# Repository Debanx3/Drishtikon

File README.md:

# Drishtikon:
## EdgeAI based human detection system <br>
 
+ The beginnings: ***Drishtikon*** is a framework consisting of two modules, the mainboard and the controller modules that can be powered directly from the 220VAC mains in dorms, libraries and canteens. The two boards communicate with each other using a BLE protocol and the mainboard is connected to the internet via Wi-Fi, it connects to the local network using hard coding.<br> <br>
  <div>

  </div>

* License: MIT License
* Contact/Credits: Debanil Chanda, [DebanX3@github.com](mailto:debanx3@github.com)

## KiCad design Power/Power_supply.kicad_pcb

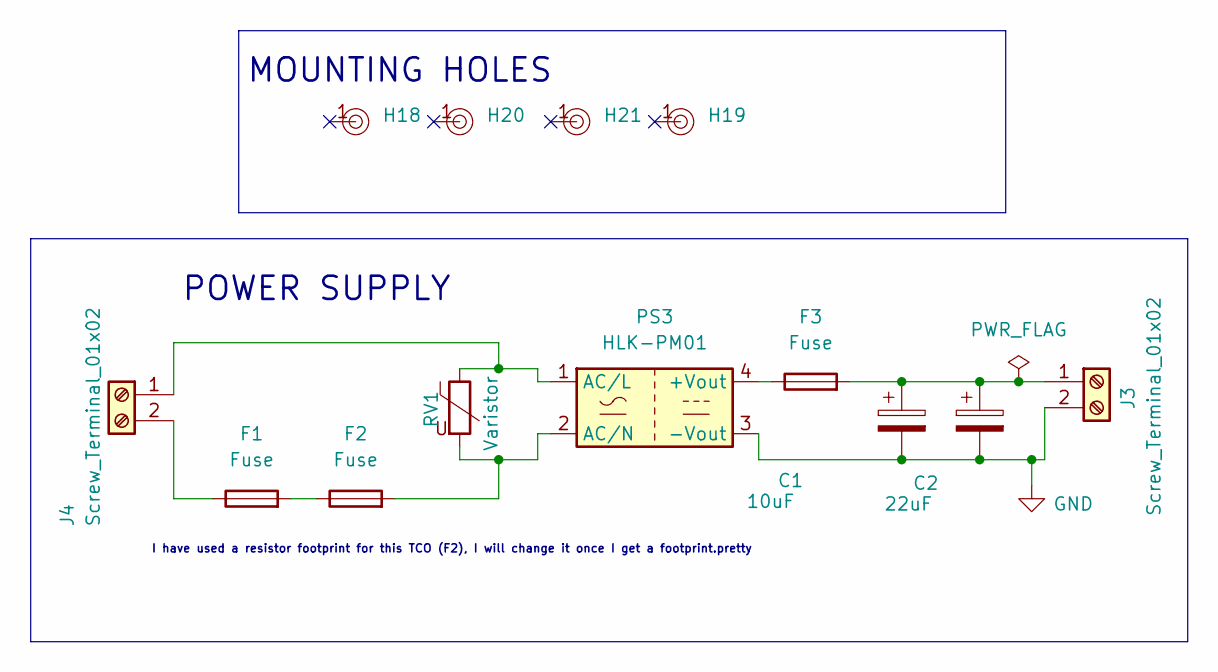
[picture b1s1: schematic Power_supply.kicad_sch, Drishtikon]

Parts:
C1: 10uF; CP_Radial_D8.0mm_P3.50mm
C2: 22uF; CP_Radial_D8.0mm_P3.50mm
F1, F3: Fuse; Fuseholder_Cylinder-5x20mm_Stelvio-Kontek_PTF78_Horizontal_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
F2: Fuse; R_Axial_DIN0309_L9.0mm_D3.2mm_P12.70mm_Horizontal
H18, H19, H20, H21: Hole, 3mm
J3, J4: Screw_Terminal_01x02; TerminalBlock_Phoenix_MKDS-1,5-2-5.08_1x02_P5.08mm_Horizont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
PS3: HLK-PM01; Converter_ACDC_Hi-Link_HLK-PMxx
RV1: Varistor; RV_Disc_D12mm_W3.9mm_P7.5mm

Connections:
GND: C1.2, C2.2, J3.2, PS3.3 (-Vout)
unnamed: F1.2, F2.1
unnamed: C1.1, C2.1, F3.2, J3.1
unnamed: J4.1, PS3.1 (AC/L), RV1.1
unnamed: F1.1, J4.2
unnamed: F3.1, PS3.4 (+Vout)
unnamed: F2.2, PS3.2 (AC/N), RV1.2

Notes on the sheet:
I have used a resistor footprint for this TCO (F2), I will change it once I get a footprint.pretty
POWER SUPPLY
MOUNTING HOLES

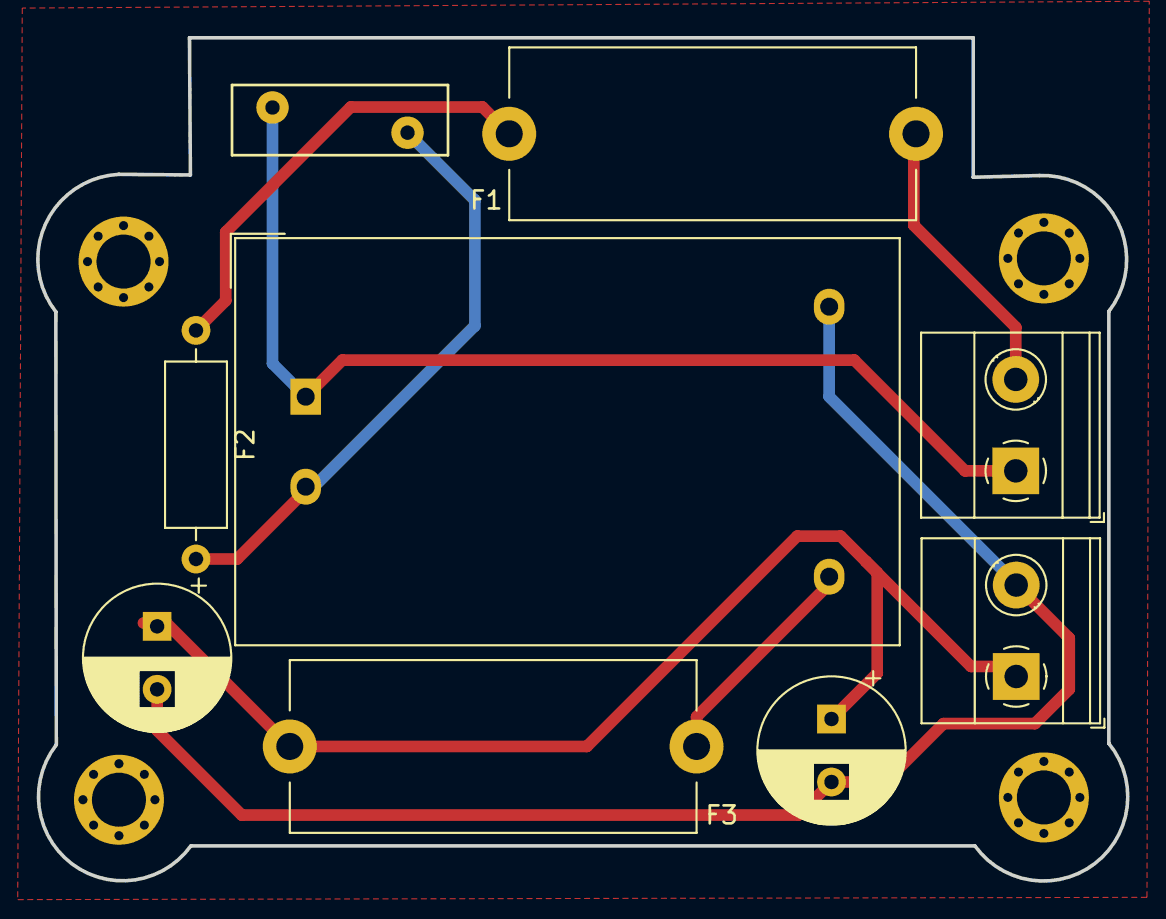
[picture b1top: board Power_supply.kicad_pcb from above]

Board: 2 copper layers, 60.6 x 46.8 mm, 13 parts (0 on the bottom side), 7 nets.

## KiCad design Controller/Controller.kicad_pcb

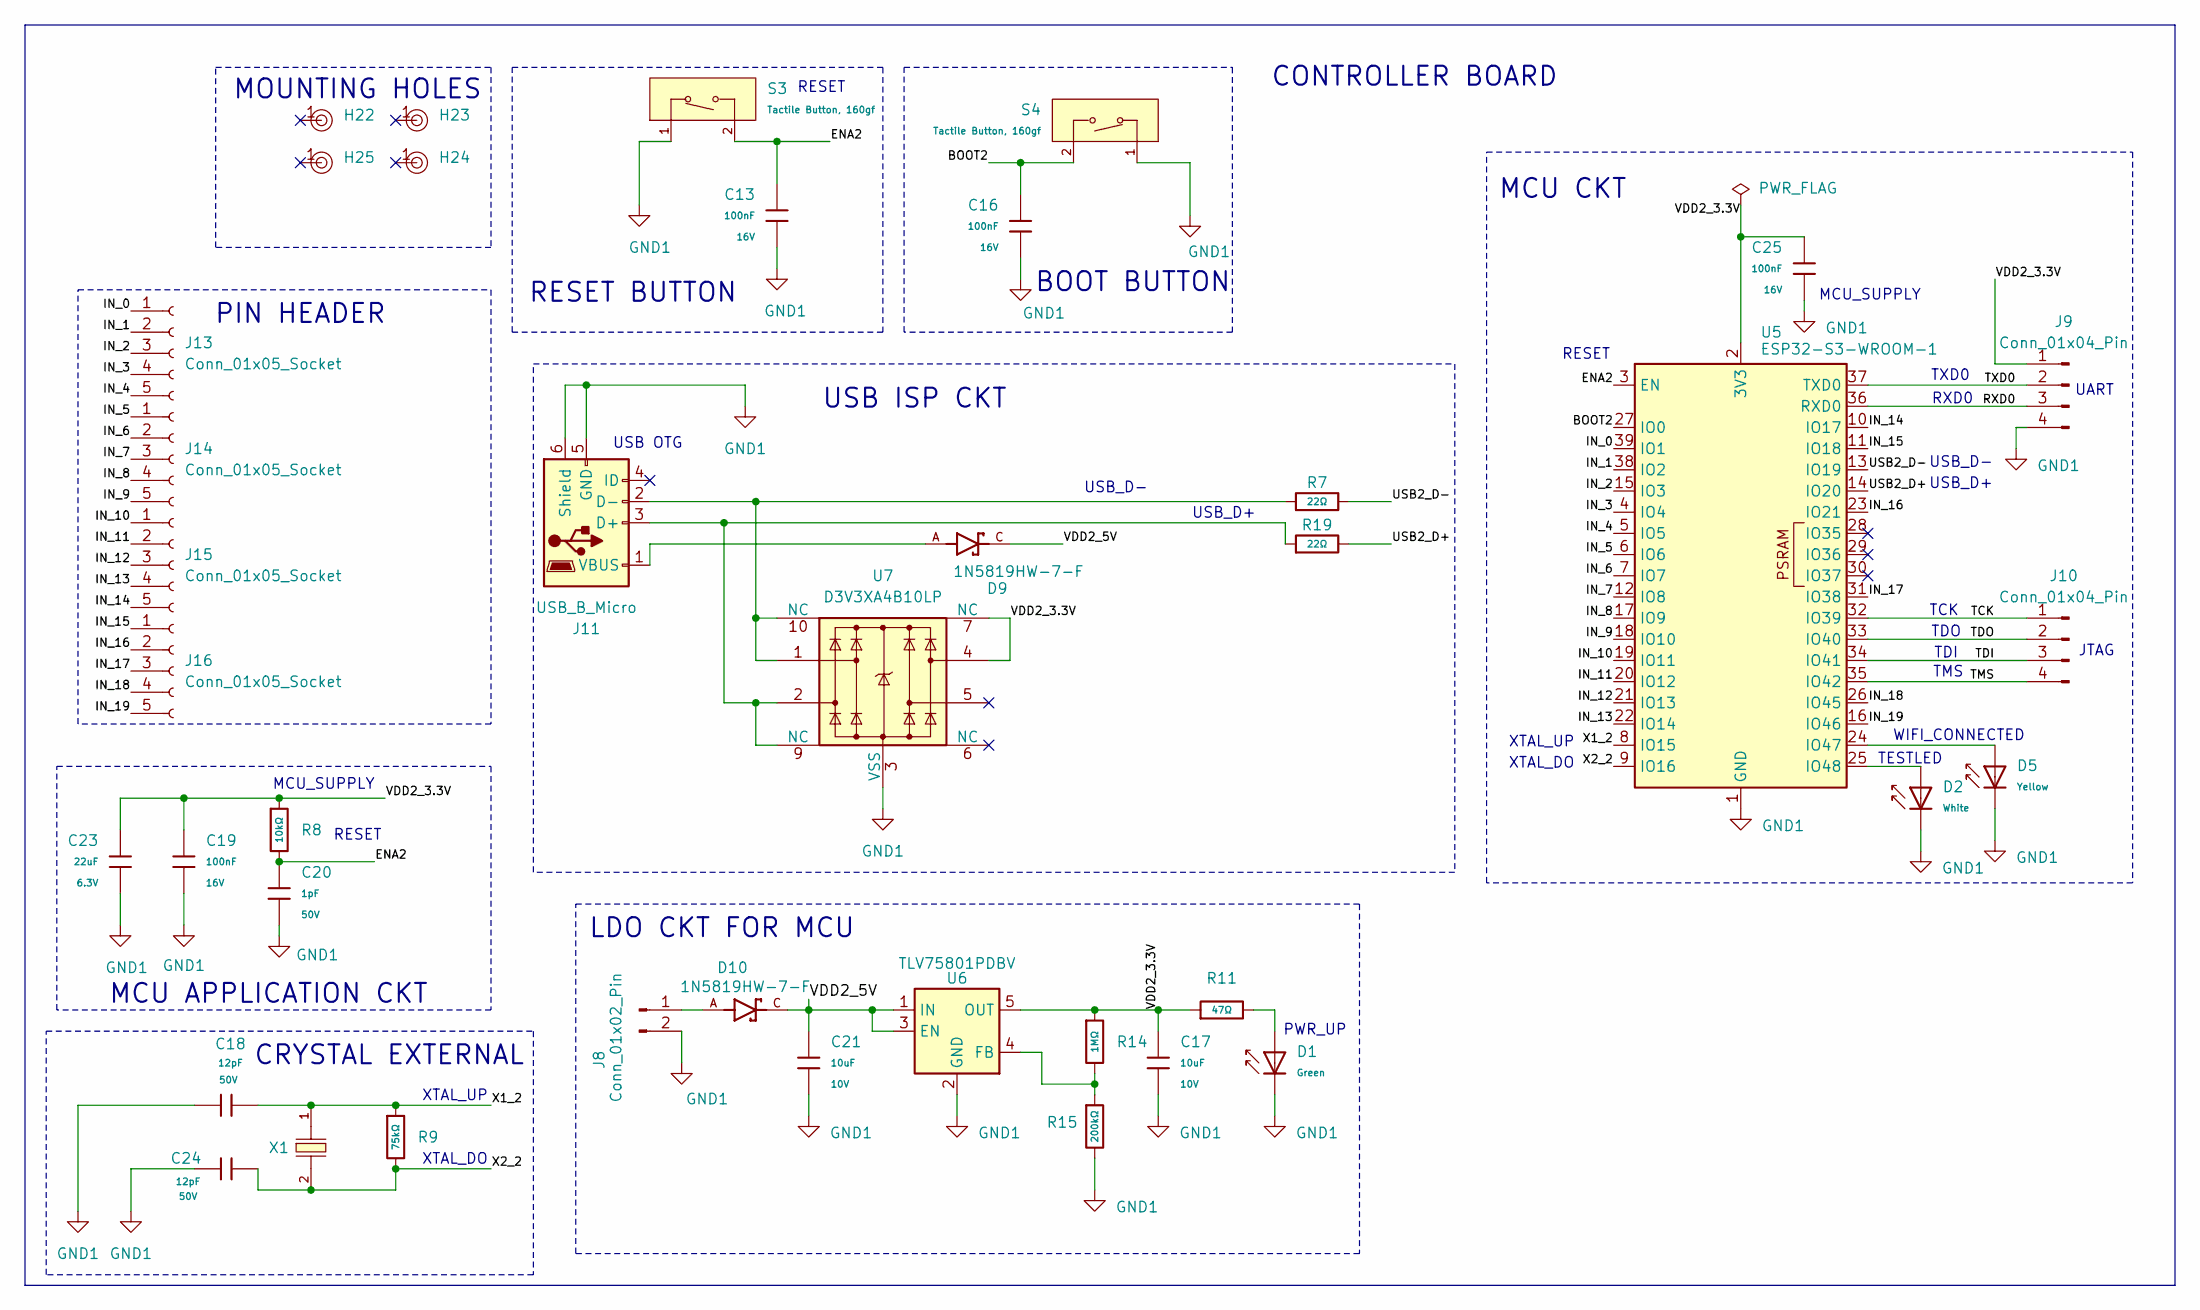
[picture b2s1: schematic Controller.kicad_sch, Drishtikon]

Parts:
C13, C16, C19, C25: 100nF; C_0402; Voltage Rated 16V; Tolerance ±10%; Part CL05B104KO5NNNC; LCSC C1525
C17, C21: 10uF; C_0603; Voltage Rated 10V; Tolerance ±10%; Part CL10A106KP8NNNC; LCSC C19702
C18, C24: 12pF; C_0402; Voltage Rated 50V; Tolerance ±5%; Part 0402CG120J500NT; LCSC C1547
C20: 1pF; C_0402; Voltage Rated 50V; Part 0402CG1R0C500NT; LCSC C1550
C23: 22uF; C_0603; Voltage Rated 6.3V; Tolerance ±20%; Part CL10A226MQ8NRNC; LCSC C59461
D1: Green; D_0805; Part KT-0805G; LCSC C2297
D2: White; D_0805; Part KT-0805W; LCSC C34499
D5: Yellow; D_0805; Part KT-0805Y; LCSC C2296
D9, D10: 1N5819HW-7-F; SOD3715X145N; PARTREV 18-2
H22, H23, H24, H25: Hole, 3mm
J8: Conn_01x02_Pin; PinHeader_1x02_P2.54mm_Horizontal
J9, J10: Conn_01x04_Pin; PinHeader_1x04_P2.54mm_Horizontal
J11: USB_B_Micro; USB_Micro-B_Molex_47346-0001
J13, J14, J15, J16: Conn_01x05_Socket; PinHeader_1x05_P2.54mm_Vertical
R7, R19: 22Ω; R_0402; Overload Voltage (Max) 50V; Tolerance ±1%; Part 0402WGF220JTCE; LCSC C25092
R8: 10kΩ; R_0402; Overload Voltage (Max) 50V; Tolerance ±1%; Part 0402WGF1002TCE; LCSC C25744
R9: 75kΩ; R_0402; Overload Voltage (Max) 50V; Tolerance ±1%; Part 0402WGF7502TCE; LCSC C25798
R11: 47Ω; R_0603; Overload Voltage (Max) 75V; Tolerance ±1%; Part 0603WAF470JT5E; LCSC C23182
R14: 1MΩ; R_0402; Overload Voltage (Max) 50V; Tolerance ±1%; Part 0402WGF1004TCE; LCSC C26083
R15: 200kΩ; R_0402; Overload Voltage (Max) 50V; Tolerance ±1%; Part 0402WGF2003TCE; LCSC C25764
S3, S4: Tactile Button, 160gf; SW_TS-1088-AR02016; Voltage Rating (Dc) 12V; Part TS-1088-AR02016; LCSC C720477
U5: ESP32-S3-WROOM-1
U6: TLV75801PDBV; SOT-23-5
U7: D3V3XA4B10LP; Diodes_UDFN-10_1.0x2.5mm_P0.5mm
X1: Q13FC1350000400; FC-135R_L3.2-W1.5; Frequency Tolerance ±20ppm; Part Q13FC13500004; LCSC C32346

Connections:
/BOOT2: C16.1, S4.2 (B), U5.27 (IO0)
/ENA2: C13.1, C20.2, R8.2, S3.2 (B), U5.3 (EN)
/IN_0: J13.1, U5.39 (IO1)
/IN_1: J13.2, U5.38 (IO2)
/IN_2: J13.3, U5.15 (IO3)
/IN_3: J13.4, U5.4 (IO4)
/IN_4: J13.5, U5.5 (IO5)
/IN_5: J14.1, U5.6 (IO6)
/IN_6: J14.2, U5.7 (IO7)
/IN_7: J14.3, U5.12 (IO8)
/IN_8: J14.4, U5.17 (IO9)
/IN_9: J14.5, U5.18 (IO10)
/IN_10: J15.1, U5.19 (IO11)
/IN_11: J15.2, U5.20 (IO12)
/IN_12: J15.3, U5.21 (IO13)
/IN_13: J15.4, U5.22 (IO14)
/IN_14: J15.5, U5.10 (IO17)
/IN_15: J16.1, U5.11 (IO18)
/IN_16: J16.2, U5.23 (IO21)
/IN_17: J16.3, U5.31 (IO38)
/IN_18: J16.4, U5.26 (IO45)
/IN_19: J16.5, U5.16 (IO46)
/RXD0: J9.3, U5.36 (RXD0)
/TCK: J10.1, U5.32 (IO39)
/TDI: J10.3, U5.34 (IO41)
/TDO: J10.2, U5.33 (IO40)
/TMS: J10.4, U5.35 (IO42)
/TXD0: J9.2, U5.37 (TXD0)
/USB2_D+: R19.2, U5.14 (IO20)
/USB2_D-: R7.2, U5.13 (IO19)
/VDD2_3.3V: C17.1, C19.1, C23.1, C25.1, J9.1, R8.1, R11.1, R14.1, U5.2 (3V3), U6.5 (OUT), U7.4, U7.7 (NC)
/VDD2_5V: C21.1, D9.C, D10.C, U6.1 (IN), U6.3 (EN)
/X1_2: C18.2, R9.1, U5.8 (IO15), X1.1
/X2_2: C24.2, R9.2, U5.9 (IO16), X1.2
GND1: C13.2, C16.2, C17.2, C18.1, C19.2, C20.1, C21.2, C23.2, C24.1, C25.2, D1.1, D2.1, D5.1, J8.2, J9.4, J11.5 (GND), J11.6 (Shield), R15.2, S3.1 (A), S4.1 (A), U5.1 (GND), U5.40 (GND), U5.41 (GND), U6.2 (GND), U7.3 (VSS), U7.8 (VSS)
unnamed: D1.2, R11.2
unnamed: D10.A, J8.1
unnamed: J11.3 (D+), R19.1, U7.2, U7.9 (NC)
unnamed: J11.2 (D-), R7.1, U7.1, U7.10 (NC)
unnamed: D9.A, J11.1 (VBUS)
unnamed: D5.2, U5.24 (IO47)
unnamed: D2.2, U5.25 (IO48)
unnamed: R14.2, R15.1, U6.4 (FB)

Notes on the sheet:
RESET
MCU_SUPPLY
UART
MCU CKT
TMS
TDI
MCU APPLICATION CKT
TDO
USB_D+
TESTLED
JTAG
BOOT BUTTON
LDO CKT FOR MCU
CONTROLLER BOARD
RESET BUTTON
WIFI_CONNECTED
MOUNTING HOLES
USB_D-
CRYSTAL EXTERNAL
XTAL_UP
PWR_UP
PIN HEADER
USB ISP CKT
USB OTG
TCK
XTAL_DO
TXD0
RXD0

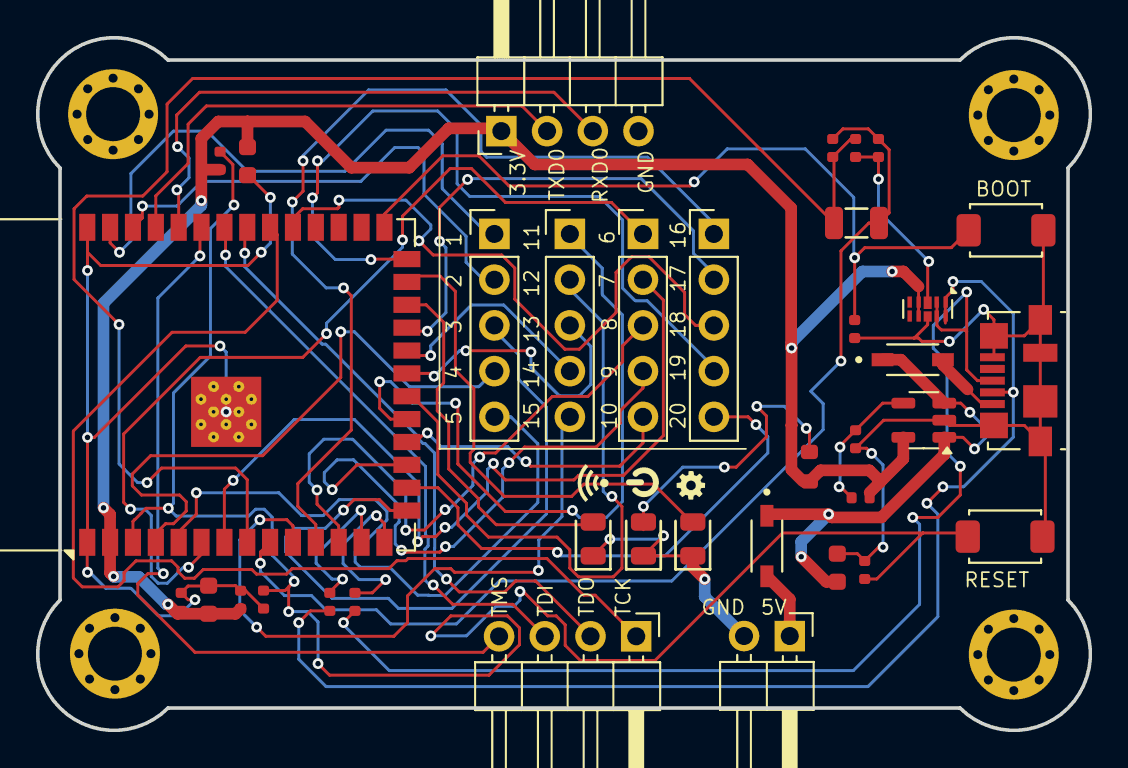
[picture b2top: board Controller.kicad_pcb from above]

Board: 4 copper layers, 58.5 x 38.5 mm, 40 parts (0 on the bottom side), 43 nets.

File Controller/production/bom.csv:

Designator,Footprint,Quantity,Value,LCSC Part #
"C13, C16, C19, C25",C_0402,4,100nF,C1525
"C17, C21",C_0603,2,10uF,C19702
"C18, C24",C_0402,2,12pF,C1547
C20,C_0402,1,1pF,C1550
C23,C_0603,1,22uF,C59461
D1,D_0805,1,Green,C2297
"D10, D9",SOD3715X145N,2,1N5819HW-7-F,
D2,D_0805,1,White,C34499
D5,D_0805,1,Yellow,C2296
"H22, H23, H24, H25","Hole, 3mm",4,~,
"J10, J9",PinHeader_1x04_P2.54mm_Horizontal,2,Conn_01x04_Pin,
J11,USB_Micro-B_Molex_47346-0001,1,USB_B_Micro,
"J13, J14, J15, J16",PinHeader_1x05_P2.54mm_Vertical,4,Conn_01x05_Socket,
J8,PinHeader_1x02_P2.54mm_Horizontal,1,Conn_01x02_Pin,
R11,R_0603,1,47Ω,C23182
R14,R_0402,1,1MΩ,C26083
R15,R_0402,1,200kΩ,C25764
"R19, R7",R_0402,2,22Ω,C25092
R8,R_0402,1,10kΩ,C25744
R9,R_0402,1,75kΩ,C25798
"S3, S4",SW_TS-1088-AR02016,2,"Tactile Button, 160gf",C720477
U5,ESP32-S3-WROOM-1,1,ESP32-S3-WROOM-1,
U6,SOT-23-5,1,TLV75801PDBV,
U7,Diodes_UDFN-10_1.0x2.5mm_P0.5mm,1,D3V3XA4B10LP,
X1,FC-135R_L3.2-W1.5,1,Q13FC1350000400,C32346

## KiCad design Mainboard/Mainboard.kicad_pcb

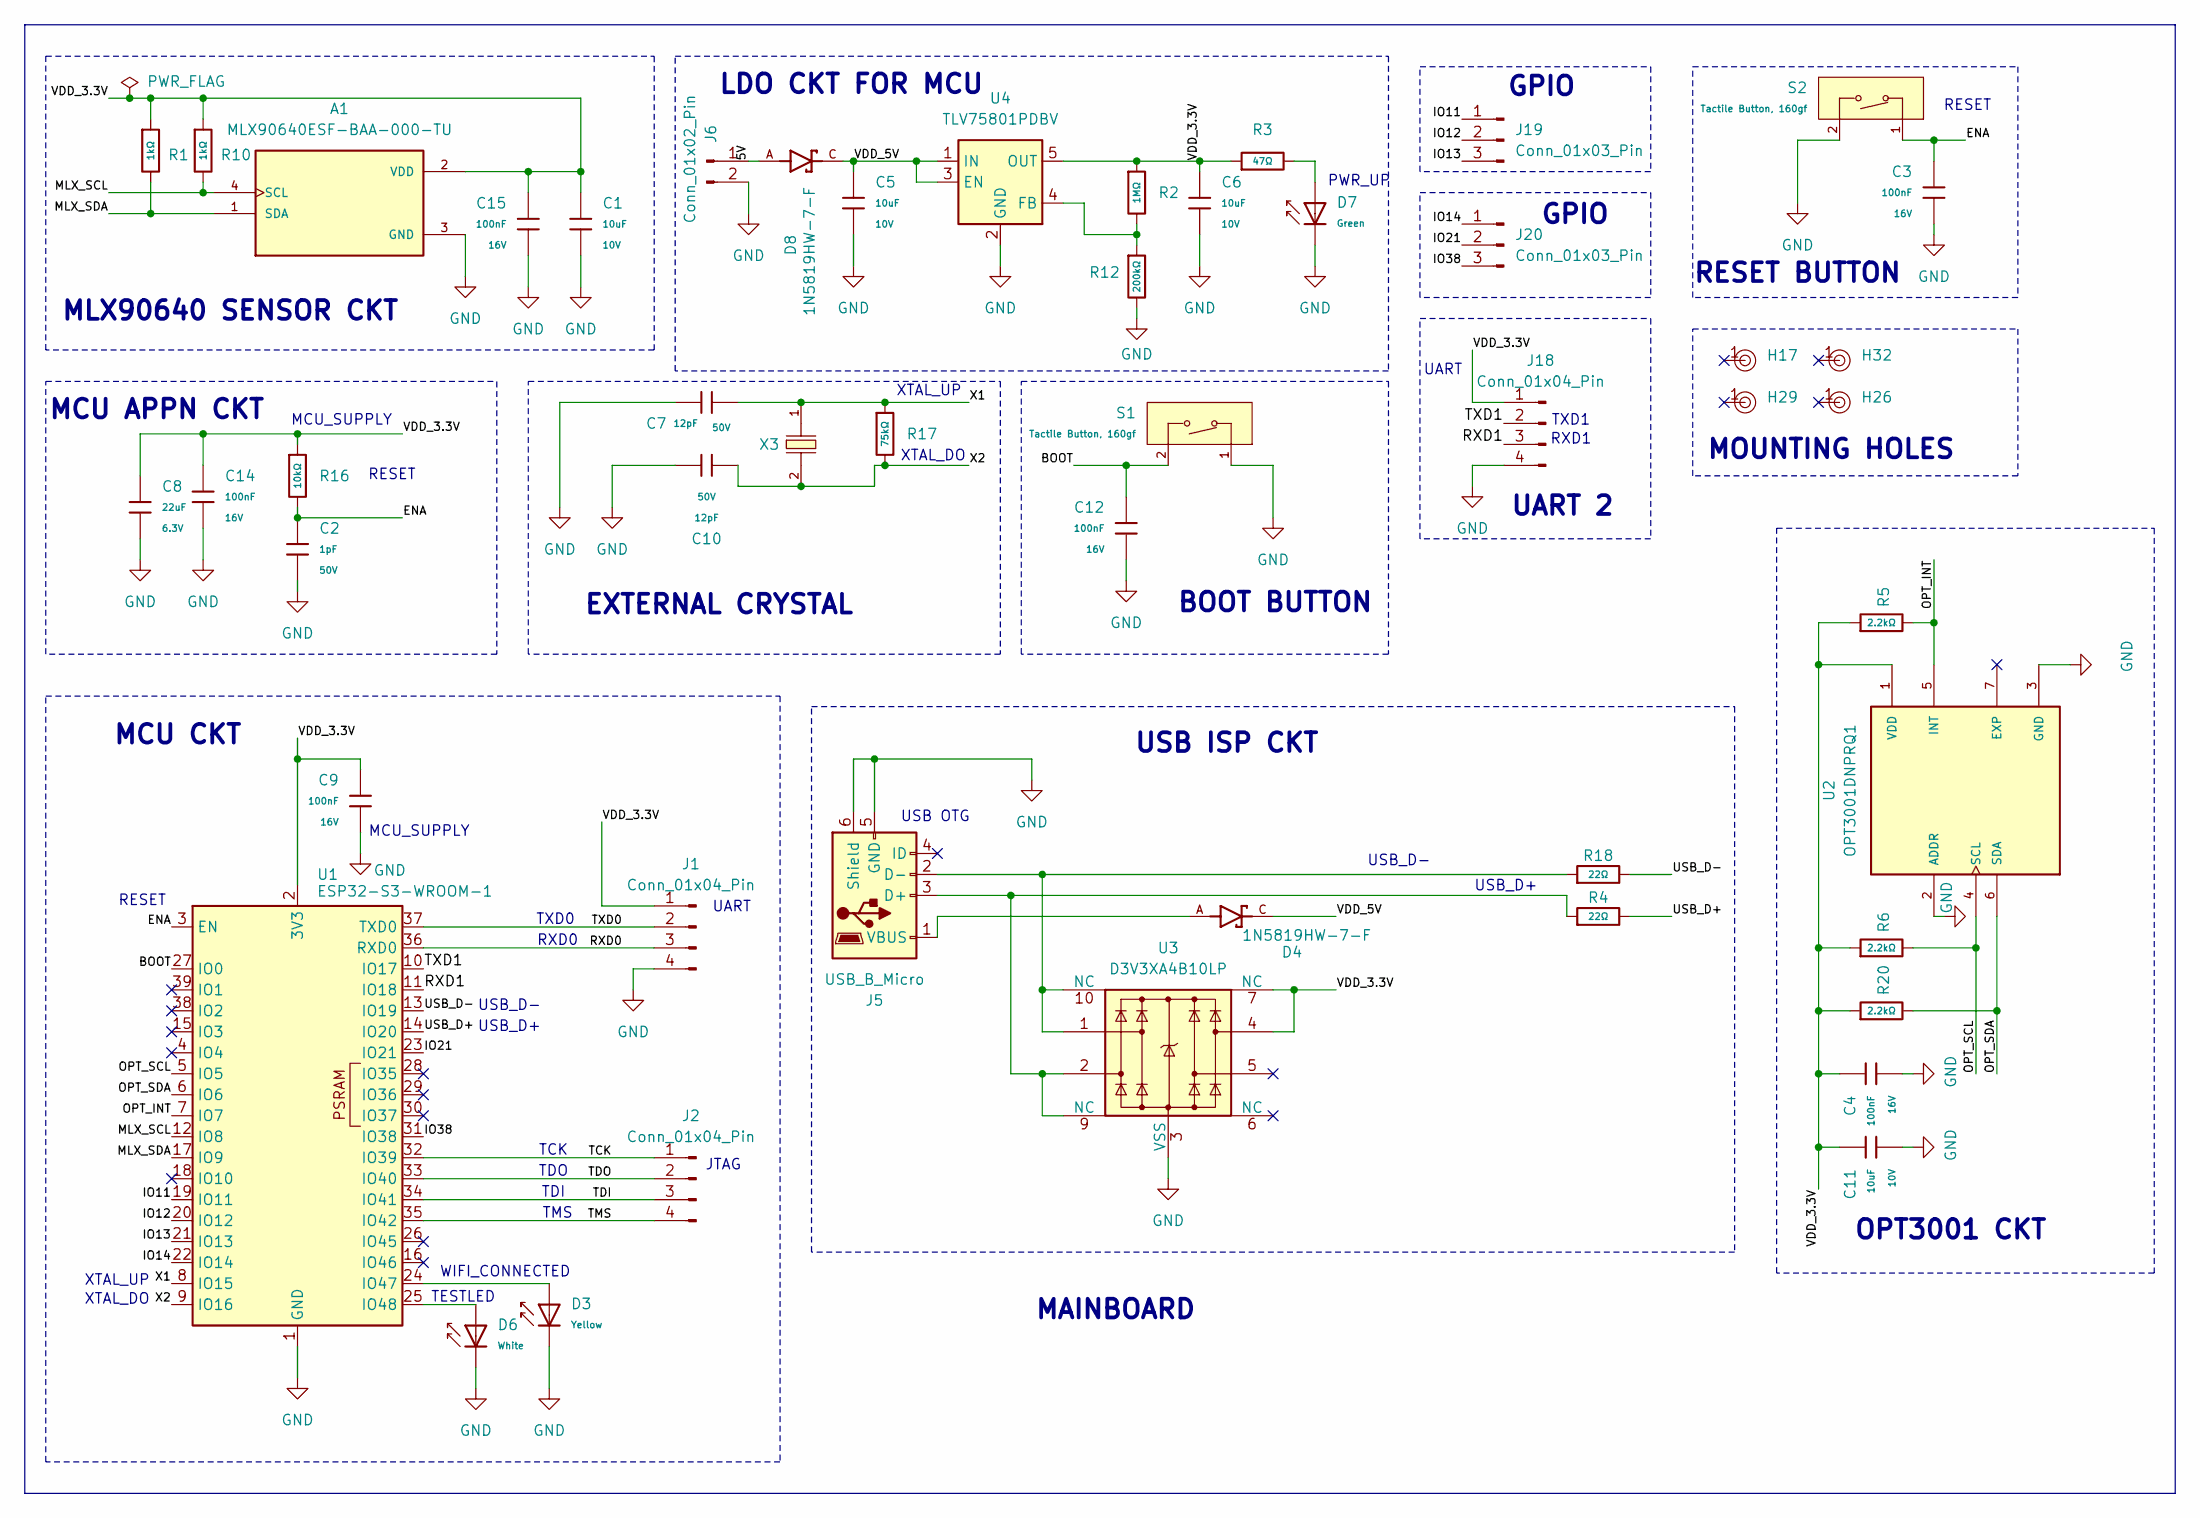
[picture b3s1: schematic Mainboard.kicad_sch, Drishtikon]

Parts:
A1: MLX90640ESF-BAA-000-TU; TO292P930H600-4; PARTREV 11
C1, C5, C6, C11: 10uF; C_0603; Voltage Rated 10V; Tolerance ±10%; Part CL10A106KP8NNNC; LCSC C19702
C2: 1pF; C_0402; Voltage Rated 50V; Part 0402CG1R0C500NT; LCSC C1550
C3, C4, C9, C12, C14, C15: 100nF; C_0402; Voltage Rated 16V; Tolerance ±10%; Part CL05B104KO5NNNC; LCSC C1525
C7, C10: 12pF; C_0402; Voltage Rated 50V; Tolerance ±5%; Part 0402CG120J500NT; LCSC C1547
C8: 22uF; C_0603; Voltage Rated 6.3V; Tolerance ±20%; Part CL10A226MQ8NRNC; LCSC C59461
D3: Yellow; D_0805; Part KT-0805Y; LCSC C2296
D4, D8: 1N5819HW-7-F; SOD3715X145N; PARTREV 18-2
D6: White; D_0805; Part KT-0805W; LCSC C34499
D7: Green; D_0805; Part KT-0805G; LCSC C2297
H17, H26, H29, H32: Hole, 3mm
J1, J2, J18: Conn_01x04_Pin; PinHeader_1x04_P2.54mm_Horizontal
J5: USB_B_Micro; USB_Micro-B_Molex_47346-0001
J6: Conn_01x02_Pin; PinHeader_1x02_P2.54mm_Horizontal
J19, J20: Conn_01x03_Pin; PinHeader_1x03_P2.54mm_Horizontal
R1, R10: 1kΩ; R_0402; Overload Voltage (Max) 50V; Tolerance ±1%; Part 0402WGF1001TCE; LCSC C11702
R2: 1MΩ; R_0402; Overload Voltage (Max) 50V; Tolerance ±1%; Part 0402WGF1004TCE; LCSC C26083
R3: 47Ω; R_0603; Overload Voltage (Max) 75V; Tolerance ±1%; Part 0603WAF470JT5E; LCSC C23182
R4, R18: 22Ω; R_0402; Overload Voltage (Max) 50V; Tolerance ±1%; Part 0402WGF220JTCE; LCSC C25092
R5, R6, R20: 2.2kΩ; R_0402; Overload Voltage (Max) 50V; Tolerance ±1%; Part 0402WGF2201TCE; LCSC C25879
R12: 200kΩ; R_0402; Overload Voltage (Max) 50V; Tolerance ±1%; Part 0402WGF2003TCE; LCSC C25764
R16: 10kΩ; R_0402; Overload Voltage (Max) 50V; Tolerance ±1%; Part 0402WGF1002TCE; LCSC C25744
R17: 75kΩ; R_0402; Overload Voltage (Max) 50V; Tolerance ±1%; Part 0402WGF7502TCE; LCSC C25798
S1, S2: Tactile Button, 160gf; SW_TS-1088-AR02016; Voltage Rating (Dc) 12V; Part TS-1088-AR02016; LCSC C720477
U1: ESP32-S3-WROOM-1
U2: OPT3001DNPRQ1; SON65P200X200X65-7N; PARTREV 01/2018
U3: D3V3XA4B10LP; Diodes_UDFN-10_1.0x2.5mm_P0.5mm
U4: TLV75801PDBV; SOT-23-5
X3: Q13FC1350000400; FC-135R_L3.2-W1.5; Frequency Tolerance ±20ppm; Part Q13FC13500004; LCSC C32346

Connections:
/5V: D8.A, J6.1
/BOOT: C12.1, S1.2 (B), U1.27 (IO0)
/ENA: C2.2, C3.1, R16.2, S2.1 (A), U1.3 (EN)
/IO11: J19.1, U1.19 (IO11)
/IO12: J19.2, U1.20 (IO12)
/IO13: J19.3, U1.21 (IO13)
/IO14: J20.1, U1.22 (IO14)
/IO21: J20.2, U1.23 (IO21)
/IO38: J20.3, U1.31 (IO38)
/MLX_SCL: A1.4 (SCL), R10.2, U1.12 (IO8)
/MLX_SDA: A1.1 (SDA), R1.2, U1.17 (IO9)
/OPT_INT: R5.2, U1.7 (IO7), U2.5 (INT)
/OPT_SCL: R6.2, U1.5 (IO5), U2.4 (SCL)
/OPT_SDA: R20.2, U1.6 (IO6), U2.6 (SDA)
/RXD0: J1.3, U1.36 (RXD0)
/RXD1: J18.3, U1.11 (IO18)
/TCK: J2.1, U1.32 (IO39)
/TDI: J2.3, U1.34 (IO41)
/TDO: J2.2, U1.33 (IO40)
/TMS: J2.4, U1.35 (IO42)
/TXD0: J1.2, U1.37 (TXD0)
/TXD1: J18.2, U1.10 (IO17)
/USB_D+: R4.2, U1.14 (IO20)
/USB_D-: R18.2, U1.13 (IO19)
/VDD_3.3V: A1.2 (VDD), C1.1, C4.1, C6.1, C8.1, C9.1, C11.1, C14.1, C15.1, J1.1, J18.1, R1.1, R2.1, R3.1, R5.1, R6.1, R10.1, R16.1, R20.1, U1.2 (3V3), U2.1 (VDD), U3.4, U3.7 (NC), U4.5 (OUT)
/VDD_5V: C5.1, D4.C, D8.C, U4.1 (IN), U4.3 (EN)
/X1: C7.2, R17.1, U1.8 (IO15), X3.1
/X2: C10.2, R17.2, U1.9 (IO16), X3.2
GND: A1.3 (GND), C1.2, C2.1, C3.2, C4.2, C5.2, C6.2, C7.1, C8.2, C9.2, C10.1, C11.2, C12.2, C14.2, C15.2, D3.1, D6.1, D7.1, J1.4, J5.5 (GND), J5.6 (Shield), J6.2, J18.4, R12.2, S1.1 (A), S2.2 (B), U1.1 (GND), U1.40 (GND), U1.41 (GND), U2.2 (ADDR), U2.3 (GND), U3.3 (VSS), U3.8 (VSS), U4.2 (GND)
unnamed: D7.2, R3.2
unnamed: J5.3 (D+), R4.1, U3.2, U3.9 (NC)
unnamed: J5.2 (D-), R18.1, U3.1, U3.10 (NC)
unnamed: D4.A, J5.1 (VBUS)
unnamed: D3.2, U1.24 (IO47)
unnamed: D6.2, U1.25 (IO48)
unnamed: R2.2, R12.1, U4.4 (FB)

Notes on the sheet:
OPT3001 CKT
LDO CKT FOR MCU
RXD0
PWR_UP
RESET
MCU_SUPPLY
MAINBOARD
XTAL_UP
GPIO
BOOT BUTTON
TDO
USB_D-
JTAG
USB ISP CKT
TXD0
UART
RXD1
MOUNTING HOLES
WIFI_CONNECTED
TCK
EXTERNAL CRYSTAL
TXD1
TDI
MCU CKT
RESET BUTTON
TESTLED
USB OTG
UART 2
XTAL_DO
MCU APPN CKT
USB_D+
TMS
MLX90640 SENSOR CKT

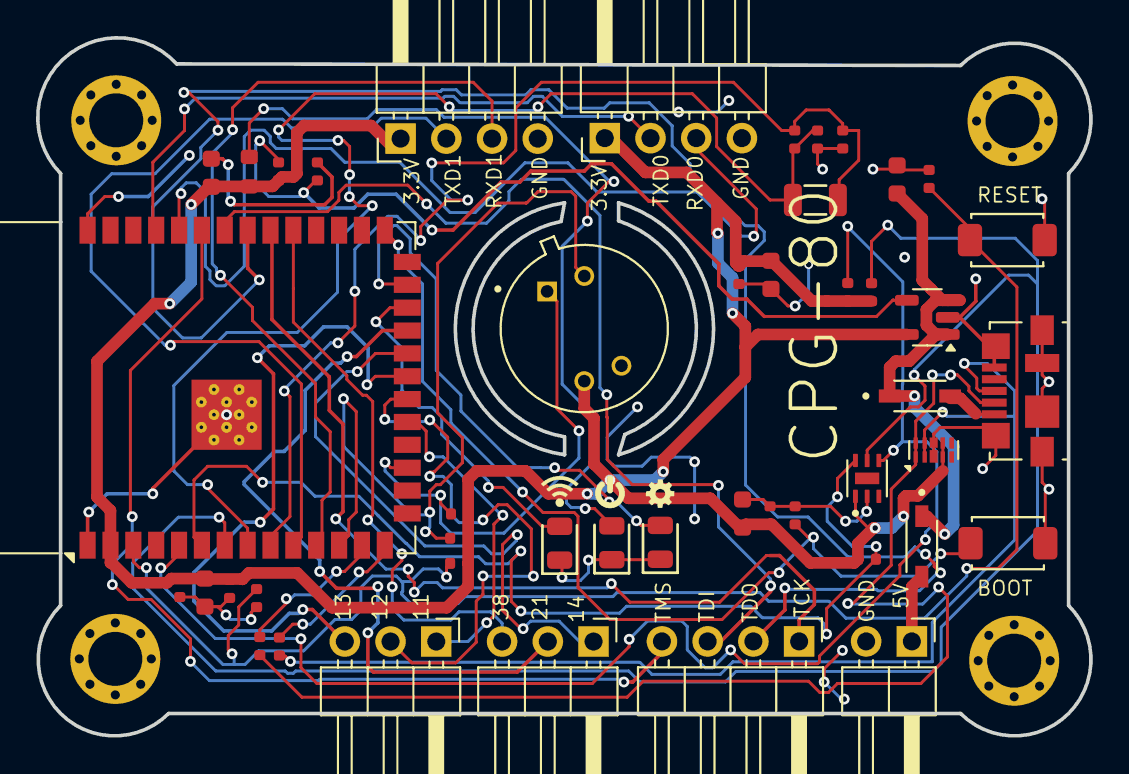
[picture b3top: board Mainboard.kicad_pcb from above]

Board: 4 copper layers, 58.5 x 38.8 mm, 50 parts (0 on the bottom side), 36 nets.

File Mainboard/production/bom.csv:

Designator,Footprint,Quantity,Value,LCSC Part #
A1,TO292P930H600-4,1,MLX90640ESF-BAA-000-TU,
"C1, C11, C5, C6",C_0603,4,10uF,C19702
"C10, C7",C_0402,2,12pF,C1547
"C12, C14, C15, C3, C4, C9",C_0402,6,100nF,C1525
C2,C_0402,1,1pF,C1550
C8,C_0603,1,22uF,C59461
D3,D_0805,1,Yellow,C2296
"D4, D8",SOD3715X145N,2,1N5819HW-7-F,
D6,D_0805,1,White,C34499
D7,D_0805,1,Green,C2297
"H17, H26, H29, H32","Hole, 3mm",4,~,
"J1, J18, J2",PinHeader_1x04_P2.54mm_Horizontal,3,Conn_01x04_Pin,
"J19, J20",PinHeader_1x03_P2.54mm_Horizontal,2,Conn_01x03_Pin,
J5,USB_Micro-B_Molex_47346-0001,1,USB_B_Micro,
J6,PinHeader_1x02_P2.54mm_Horizontal,1,Conn_01x02_Pin,
"R1, R10",R_0402,2,1kΩ,C11702
R12,R_0402,1,200kΩ,C25764
R16,R_0402,1,10kΩ,C25744
R17,R_0402,1,75kΩ,C25798
"R18, R4",R_0402,2,22Ω,C25092
R2,R_0402,1,1MΩ,C26083
"R20, R5, R6",R_0402,3,2.2kΩ,C25879
R3,R_0603,1,47Ω,C23182
"S1, S2",SW_TS-1088-AR02016,2,"Tactile Button, 160gf",C720477
U1,ESP32-S3-WROOM-1,1,ESP32-S3-WROOM-1,
U2,SON65P200X200X65-7N,1,OPT3001DNPRQ1,
U3,Diodes_UDFN-10_1.0x2.5mm_P0.5mm,1,D3V3XA4B10LP,
U4,SOT-23-5,1,TLV75801PDBV,
X3,FC-135R_L3.2-W1.5,1,Q13FC1350000400,C32346

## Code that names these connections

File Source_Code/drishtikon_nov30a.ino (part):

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
// --- PIN DEFINITIONS ---
// I2C Bus 1: MLX90640 (Kept on standard 'Wire' object)
#define MLX_SDA_PIN 8
#define MLX_SCL_PIN 9

// I2C Bus 2: OPT3001 (Moved to custom 'Wire_OPT' object)
#define OPT_SDA_PIN 11
#define OPT_SCL_PIN 10
#define OPT_INT_PIN 12

// ... (rest of the #defines for TF and global variables)

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
    // 1. --- I2C Initialization for MLX90640 (Pins 8, 9) ---
    // The standard 'Wire' object is used and initialized to MLX pins.
    Wire.begin(MLX_SDA_PIN, MLX_SCL_PIN);

    Serial.println("TENSORFLOW THERMAL OBJECT DETECTION");
    Serial.print("MLX Bus (Wire): SDA: GPIO "); Serial.print(MLX_SDA_PIN);
    Serial.print(", SCL: GPIO "); Serial.println(MLX_SCL_PIN);

    // Initialize MLX90640, passing the standard '&Wire' object
    if (!mlx.begin(MLX90640_I2CADDR_DEFAULT, &Wire)) {
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
    // 2. --- I2C Initialization for OPT3001 (Pins 10, 11) ---
    // The custom 'Wire_OPT' object is initialized here.
    Wire_OPT.begin(OPT_SDA_PIN, OPT_SCL_PIN, 100000);
    pinMode(OPT_INT_PIN, INPUT_PULLUP);


    Serial.println("\nOPT3001 Sensor Initialization");
    Serial.print("OPT Bus (Wire_OPT): SDA: GPIO "); Serial.print(OPT_SDA_PIN);
    Serial.print(", SCL: GPIO "); Serial.println(OPT_SCL_PIN);

    // Setup the OPT3001, passing the custom 'Wire_OPT' object
    // 2. --- I2C Initialization for OPT3001 (Pins 10, 11 using Wire_OPT) ---
// ... (Wire_OPT.begin() and pinMode(OPT_INT_PIN) remain here) ...

// Setup the OPT3001, passing the custom 'Wire_OPT' object
if (sensor.setup(Wire_OPT, I2C_ADDRESS) != 0) {
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
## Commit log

2025-10-20 Enhance README with project details and structure
    Expanded project description and added module details.
2025-10-20 Add initial documentation file
    Project documentation folder
2025-10-20 new commit at 02:53 PM @20th october 2025
    Schematics, Layouts and 3D models
2025-10-20 Update README with Power-supply section and images
    Added a Power-supply section and updated images in README.
2025-10-20 Fix image link for Drishtikon in README
    Updated image link for Drishtikon in README.
2025-10-20 Update Mainboard image and add Power supply section
    Updated images for Mainboard and added Power supply section.
2025-10-20 Fix formatting and update README content
2025-10-20 Add image link for Controller in README
2025-10-20 Update README with more images for components
    Added additional images for Mainboard, Controller, and Power supply sections.
2025-10-20 Revise project title and description in README
    Updated project title and clarified description.
2025-10-20 Update README with additional images for components
2025-10-20 Fix image links for Mainboard PCB in README
    Updated image links for the Mainboard PCB in README.
2025-10-20 Comment out unused images in README
    Commented out unused image links for mainboard, controller, and power supply.
2025-10-20 Add Mainboard documentation file
2025-10-20 Add initial Controller documentation
2025-10-20 Add initial Power Supply documentation
2025-10-20 Mainboard init commit KiCad files
    KiCad files
2025-10-20 Controller init KiCad files
    KiCad files
2025-10-20 Power supply init KiCad files
    KiCad files
2025-10-20 Refactor README formatting and structure
    Updated the README to improve formatting and structure, including adding HTML line breaks and correcting header levels.
2025-10-26 Update images in README and remove empty entries
2025-10-26 Fix image order and alt text in README.md
2025-10-28 Update image links in README.md
    Removed an image link and added a new one in the README.
2025-10-28 Fix image source formatting in README.md
2025-10-28 Update image dimensions and add new image
2025-10-28 Update README with license and contact details
    Added license and contact information to README.
2025-10-28 Fix license section formatting in README.md
2025-10-30 Add new image to README.md
2025-12-01 Create video.md
    video implementation of the Drishtikon
2025-12-02 Add frontend UI documentation
2025-12-02 Add README for Python scripts capturing MLX90640 data

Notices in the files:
Controller/Controller.kicad_pcb:
creativecommons.org/licenses/by/4.0
Licence: CC by 4.0
Controller/Controller.kicad_sch:
License: CC by 4.0
